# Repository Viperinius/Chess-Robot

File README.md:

# Chess-Robot

## Structure Overview

## Frame Design
Currently draft only:

## Current Schematic and PCB

## Used libraries / Libraries needed to run
- Used for programming web page, Stockfish & Arduino bridge:
    + [Adafruit MCP23017 Library](https://github.com/adafruit/Adafruit-MCP23017-Arduino-Library)
    + [chess.js](https://github.com/jhlywa/chess.js)
    + [chessboardjs](https://github.com/oakmac/chessboardjs/)
    + [Stockfish](https://github.com/official-stockfish/Stockfish)
    + [stockfish Python package](https://github.com/zhelyabuzhsky/stockfish)
- Used for schematic / PCB layout (KiCad):
    + [arduino_nano](https://github.com/kiwichrish/kicad_ArduinoNano)

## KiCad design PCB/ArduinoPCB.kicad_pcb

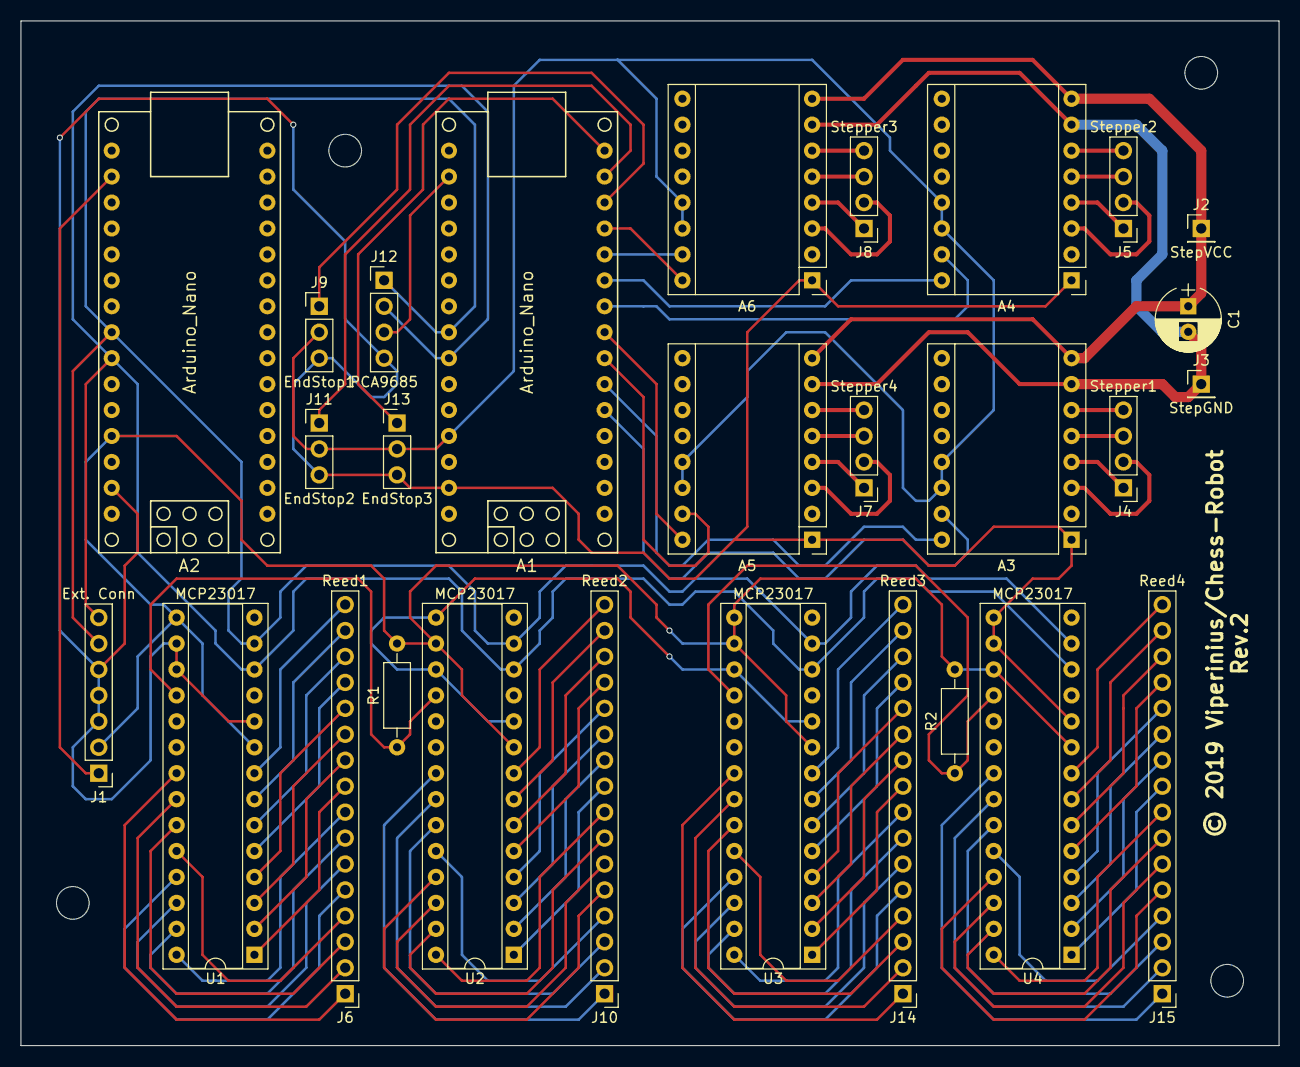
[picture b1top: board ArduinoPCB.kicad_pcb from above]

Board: 2 copper layers, 123.2 x 100.3 mm, 28 parts (0 on the bottom side), 102 nets.

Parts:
A1, A2: Arduino_Nano; arduino_nano
A3, A4, A5, A6: Pololu_Breakout_DRV8825; Pololu_Breakout-16_15.2x20.3mm
C1: CP; CP_Radial_D6.3mm_P2.50mm
J1: Ext. Conn; Pin_Header_Straight_1x07_Pitch2.54mm
J2: StepVCC; Pin_Header_Straight_1x01_Pitch2.54mm
J3: StepGND; Pin_Header_Straight_1x01_Pitch2.54mm
J4: Stepper1; Pin_Header_Straight_1x04_Pitch2.54mm
J5: Stepper2; Pin_Header_Straight_1x04_Pitch2.54mm
J6: Reed1; Pin_Header_Straight_1x16_Pitch2.54mm
J7: Stepper4; Pin_Header_Straight_1x04_Pitch2.54mm
J8: Stepper3; Pin_Header_Straight_1x04_Pitch2.54mm
J9: EndStop1; Pin_Header_Straight_1x03_Pitch2.54mm
J10: Reed2; Pin_Header_Straight_1x16_Pitch2.54mm
J11: EndStop2; Pin_Header_Straight_1x03_Pitch2.54mm
J12: PCA9685; Pin_Header_Straight_1x04_Pitch2.54mm
J13: EndStop3; Pin_Header_Straight_1x03_Pitch2.54mm
J14: Reed3; Pin_Header_Straight_1x16_Pitch2.54mm
J15: Reed4; Pin_Header_Straight_1x16_Pitch2.54mm
R1, R2: 10k; R_Axial_DIN0207_L6.3mm_D2.5mm_P10.16mm_Horizontal
U1, U2, U3, U4: MCP23017; DIP-28_W7.62mm_Socket

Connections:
3V3: A2.17, J1.1
3V3_2: A1.17, J12.3
5V: A2.27, J1.2, R1.2, R2.2, U1.9, U1.15, U2.9, U2.16, U3.9, U3.15, U3.16, U4.9, U4.17
5V_2: A1.27, A3.13, A3.14, A4.13, A4.14, A5.13, A5.14, A6.13, A6.14, J9.2, J11.2, J13.2
8V+: A3.8, A4.8, A5.8, A6.8, C1.1, J2.1
8V_GND: A3.7, A4.7, A5.7, A6.7, C1.2, J3.1
GND: A1.29, A2.29, A3.1, A4.1, A5.1, A6.1, J1.3, J1.4, J1.5, J9.3, J11.3, J12.4, J13.3, U1.10, U1.16, U1.17, U2.10, U2.15, U2.17, U3.10, U3.17, U4.10, U4.15, U4.16
unnamed: A1.5, A3.15
unnamed: A1.6, A3.16
unnamed: A1.7, A5.15
unnamed: A1.8, A5.16
unnamed: A1.9, A4.15
unnamed: A1.10, A4.16
unnamed: A1.11, A6.15
unnamed: A1.12, A6.16
unnamed: A1.13, J9.1
unnamed: A1.14, J11.1
unnamed: A1.15, J13.1
unnamed: A3.3, J4.2
unnamed: A3.4, J4.1
unnamed: A3.5, J4.3
unnamed: A3.6, J4.4
unnamed: A4.3, J5.2
unnamed: A4.4, J5.1
unnamed: A4.5, J5.3
unnamed: A4.6, J5.4
unnamed: A5.3, J7.2
unnamed: A5.4, J7.1
unnamed: A5.5, J7.3
unnamed: A5.6, J7.4
unnamed: A6.3, J8.2
unnamed: A6.4, J8.1
unnamed: A6.5, J8.3
unnamed: A6.6, J8.4
unnamed: J6.1, U1.21
unnamed: J6.2, U1.22
unnamed: J6.3, U1.23
unnamed: J6.4, U1.24
unnamed: J6.5, U1.25
unnamed: J6.6, U1.26
unnamed: J6.7, U1.27
unnamed: J6.8, U1.28
unnamed: J6.9, U1.1
unnamed: J6.10, U1.2
unnamed: J6.11, U1.3
unnamed: J6.12, U1.4
unnamed: J6.13, U1.5
unnamed: J6.14, U1.6
unnamed: J6.15, U1.7
unnamed: J6.16, U1.8
unnamed: J10.1, U2.21
unnamed: J10.2, U2.22
unnamed: J10.3, U2.23
unnamed: J10.4, U2.24
unnamed: J10.5, U2.25
unnamed: J10.6, U2.26
unnamed: J10.7, U2.27
unnamed: J10.8, U2.28
unnamed: J10.9, U2.1
unnamed: J10.10, U2.2
unnamed: J10.11, U2.3
unnamed: J10.12, U2.4
unnamed: J10.13, U2.5
unnamed: J10.14, U2.6
unnamed: J10.15, U2.7
unnamed: J10.16, U2.8
unnamed: J14.1, U3.21
unnamed: J14.2, U3.22
unnamed: J14.3, U3.23
unnamed: J14.4, U3.24
unnamed: J14.5, U3.25
unnamed: J14.6, U3.26
unnamed: J14.7, U3.27
unnamed: J14.8, U3.28
unnamed: J14.9, U3.1
unnamed: J14.10, U3.2
unnamed: J14.11, U3.3
unnamed: J14.12, U3.4
unnamed: J14.13, U3.5
unnamed: J14.14, U3.6
unnamed: J14.15, U3.7
unnamed: J14.16, U3.8
unnamed: J15.1, U4.21
unnamed: J15.2, U4.22
unnamed: J15.3, U4.23
unnamed: J15.4, U4.24
unnamed: J15.5, U4.25
unnamed: J15.6, U4.26
unnamed: J15.7, U4.27
unnamed: J15.8, U4.28
unnamed: J15.9, U4.1
unnamed: J15.10, U4.2
unnamed: J15.11, U4.3
unnamed: J15.12, U4.4
unnamed: J15.13, U4.5
unnamed: J15.14, U4.6
unnamed: J15.15, U4.7
unnamed: J15.16, U4.8
Pullup: R1.1, U1.18, U2.18
Pullup2: R2.1, U3.18, U4.18
SCL: A1.24, A2.24, J1.7, J12.2, U1.12, U2.12, U3.12, U4.12
SDA: A1.23, A2.23, J1.6, J12.1, U1.13, U2.13, U3.13, U4.13

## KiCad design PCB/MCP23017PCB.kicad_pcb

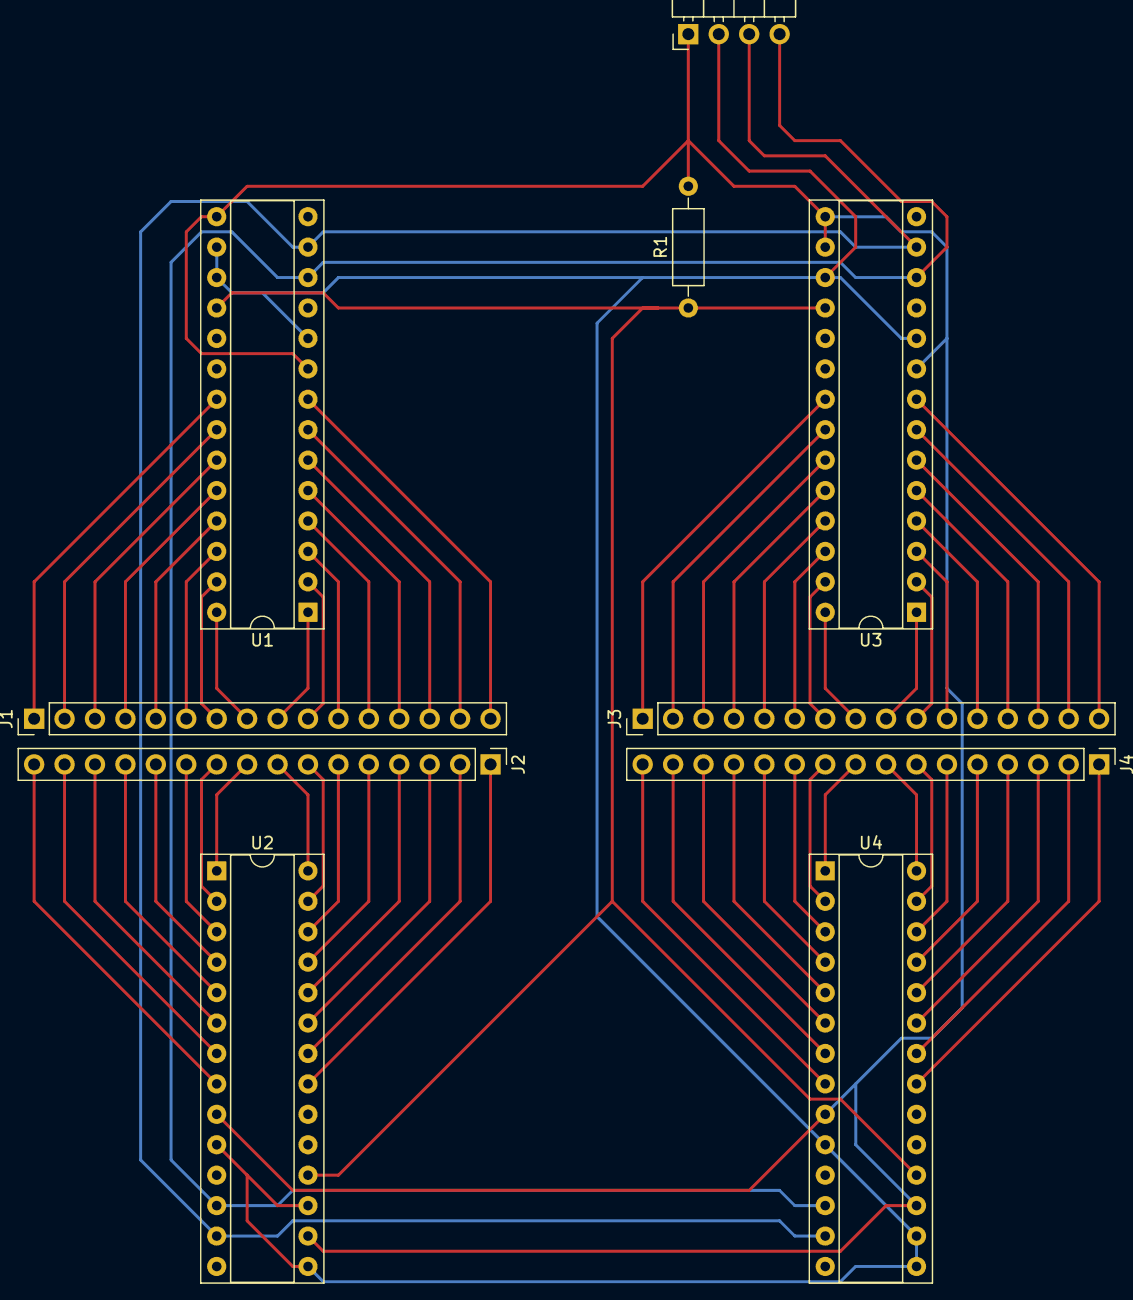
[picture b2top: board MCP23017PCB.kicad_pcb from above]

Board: 2 copper layers, 10 parts (0 on the bottom side), 69 nets.

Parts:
J1, J2, J3, J4: Conn_01x16; Pin_Header_Straight_1x16_Pitch2.54mm
J5: Conn_01x04; Pin_Header_Angled_1x04_Pitch2.54mm
R1: 10k; R_Axial_DIN0207_L6.3mm_D2.5mm_P10.16mm_Horizontal
U1, U2, U3, U4: MCP23017; DIP-28_W7.62mm_Socket

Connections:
+5V: J5.1, R1.2, U1.9, U1.15, U2.9, U2.16, U3.9, U3.15, U3.16, U4.9, U4.17
GND: J5.2, U1.10, U1.16, U1.17, U2.10, U2.15, U2.17, U3.10, U3.17, U4.10, U4.15, U4.16
unnamed: J1.1, U1.21
unnamed: J1.2, U1.22
unnamed: J1.3, U1.23
unnamed: J1.4, U1.24
unnamed: J1.5, U1.25
unnamed: J1.6, U1.26
unnamed: J1.7, U1.27
unnamed: J1.8, U1.28
unnamed: J1.9, U1.1
unnamed: J1.10, U1.2
unnamed: J1.11, U1.3
unnamed: J1.12, U1.4
unnamed: J1.13, U1.5
unnamed: J1.14, U1.6
unnamed: J1.15, U1.7
unnamed: J1.16, U1.8
unnamed: J2.1, U2.21
unnamed: J2.2, U2.22
unnamed: J2.3, U2.23
unnamed: J2.4, U2.24
unnamed: J2.5, U2.25
unnamed: J2.6, U2.26
unnamed: J2.7, U2.27
unnamed: J2.8, U2.28
unnamed: J2.9, U2.1
unnamed: J2.10, U2.2
unnamed: J2.11, U2.3
unnamed: J2.12, U2.4
unnamed: J2.13, U2.5
unnamed: J2.14, U2.6
unnamed: J2.15, U2.7
unnamed: J2.16, U2.8
unnamed: J3.1, U3.21
unnamed: J3.2, U3.22
unnamed: J3.3, U3.23
unnamed: J3.4, U3.24
unnamed: J3.5, U3.25
unnamed: J3.6, U3.26
unnamed: J3.7, U3.27
unnamed: J3.8, U3.28
unnamed: J3.9, U3.1
unnamed: J3.10, U3.2
unnamed: J3.11, U3.3
unnamed: J3.12, U3.4
unnamed: J3.13, U3.5
unnamed: J3.14, U3.6
unnamed: J3.15, U3.7
unnamed: J3.16, U3.8
unnamed: J4.1, U4.21
unnamed: J4.2, U4.22
unnamed: J4.3, U4.23
unnamed: J4.4, U4.24
unnamed: J4.5, U4.25
unnamed: J4.6, U4.26
unnamed: J4.7, U4.27
unnamed: J4.8, U4.28
unnamed: J4.9, U4.1
unnamed: J4.10, U4.2
unnamed: J4.11, U4.3
unnamed: J4.12, U4.4
unnamed: J4.13, U4.5
unnamed: J4.14, U4.6
unnamed: J4.15, U4.7
unnamed: J4.16, U4.8
Pullup: R1.1, U1.18, U2.18, U3.18, U4.18
SCL: J5.4, U1.12, U2.12, U3.12, U4.12
SDA: J5.3, U1.13, U2.13, U3.13, U4.13

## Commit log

2019-08-18 initialised directory structure
2019-08-19 first webpage ideas
2019-08-20 added basic board functions to the webpage
2019-08-21 added more chess.js functions added structure-diagram
2019-08-23 added stockfishBridge.py
2019-08-25 added first version of Arduino Python communication (Python side)
2019-08-27 added first functions for sensor reading and init functions
2019-08-30 filled sensor arduino loop with first draft, added functions for serial comms
2019-08-31 removed wrongfully added header file
2019-08-31 testing with MCPs, added first PCB try
2019-09-24 added first complete schematic and PCB version
2019-09-25 Rev2 of PCB
2019-09-28 minimal PCB changes to be able to manufacture it, added image
2019-10-02 added first frame design draft and belt-guide-holder
2019-10-03 adding more stl files
2019-10-12 added arduino code documentation, added end stop implementation, fixed readSerial
2019-10-12 fixed Arduino indenting

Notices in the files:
PCB/ArduinoPCB.kicad_pcb:
© 2019 Viperinius/Chess-Robot
